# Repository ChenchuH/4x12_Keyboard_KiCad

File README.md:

# 4x12_Keyboard_KiCad
4x12 RP2040 Keyboard

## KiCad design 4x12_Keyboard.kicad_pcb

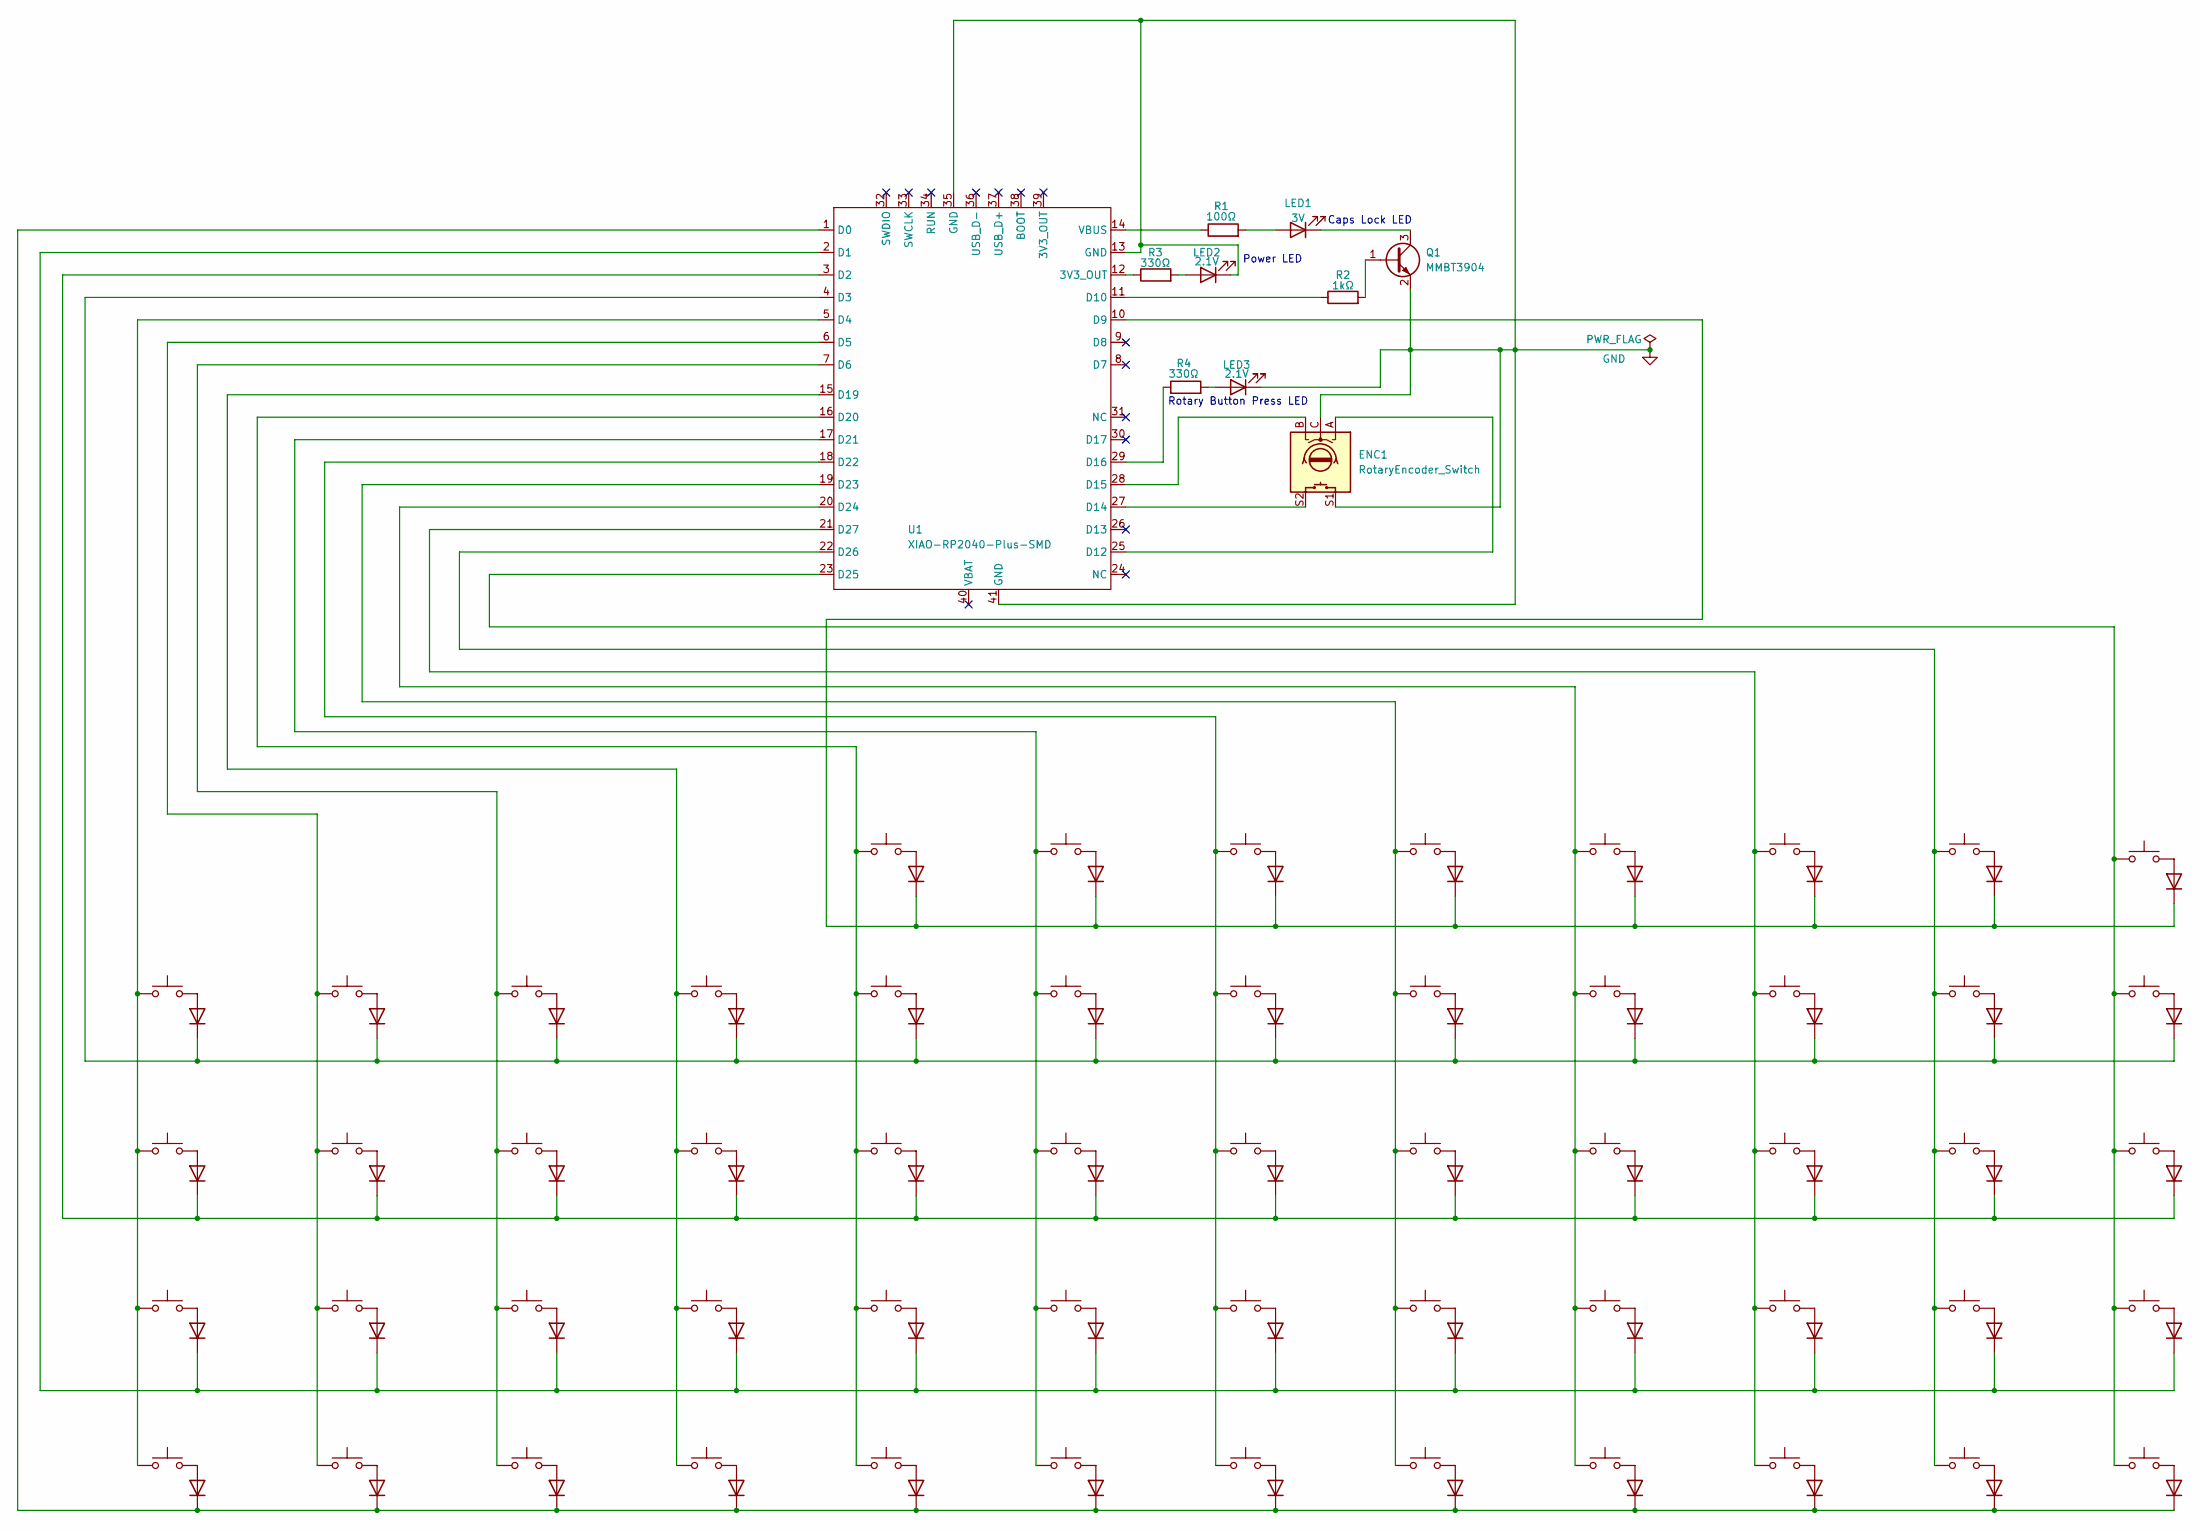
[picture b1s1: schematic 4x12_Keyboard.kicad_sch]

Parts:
D1, D2, D3, D4, D5, D6, D7, D8, D9, D10, D11, D12, D13, D14, D15, D16, D17, D18, D19, D20, D21, D22, D23, D24, D25, D26, D27, D28, D29, D30, D31, D32, D33, D34, D35, D36, D37, D38, D39, D40, D41, D42, D43, D44, D45, D46, D47, D48, D49, D50, D51, D52, D53, D54, D55, D56: D; D_SOD-123
ENC1: RotaryEncoder_Switch; RotaryEncoder_Alps_EC11E-Switch_Vertical_H20mm
LED1: 3V; LED_0805_2012Metric_Pad1.15x1.40mm_HandSolder
LED2, LED3: 2.1V; LED_0805_2012Metric_Pad1.15x1.40mm_HandSolder
Q1: MMBT3904; SOT-23
R1: 100Ω; R_0805_2012Metric_Pad1.20x1.40mm_HandSolder
R2: 1kΩ; R_0805_2012Metric_Pad1.20x1.40mm_HandSolder
R3, R4: 330Ω; R_0805_2012Metric_Pad1.20x1.40mm_HandSolder
SW1, SW2, SW3, SW4, SW5, SW6, SW7, SW8, SW9, SW10, SW11, SW12, SW13, SW14, SW15, SW16, SW17, SW18, SW19, SW20, SW21, SW22, SW23, SW24, SW25, SW26, SW27, SW28, SW29, SW30, SW31, SW32, SW33, SW34, SW35, SW36, SW37, SW38, SW39, SW40, SW41, SW42, SW43, SW44, SW45, SW46, SW47, SW48, SW49, SW50, SW51, SW52, SW53, SW54, SW55, SW56: SW_Push; SW_Cherry_MX_1.00u_PCB
U1: XIAO-RP2040-Plus-SMD

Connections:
GND: ENC1.C, ENC1.S1, LED2.1 (K), LED3.1 (K), Q1.2 (E), U1.13 (GND), U1.35 (GND), U1.41 (GND)
unnamed: D1.2 (A), SW1.2
unnamed: D1.1 (K), D5.1 (K), D9.1 (K), D13.1 (K), D17.1 (K), D21.1 (K), D25.1 (K), D29.1 (K), D33.1 (K), D37.1 (K), D41.1 (K), D45.1 (K), U1.4 (D3)
unnamed: D2.2 (A), SW2.2
unnamed: D3.2 (A), SW3.2
unnamed: D4.2 (A), SW4.2
unnamed: D5.2 (A), SW5.2
unnamed: D6.2 (A), SW6.2
unnamed: D7.2 (A), SW7.2
unnamed: D8.2 (A), SW8.2
unnamed: D9.2 (A), SW9.2
unnamed: D10.2 (A), SW10.2
unnamed: D2.1 (K), D6.1 (K), D10.1 (K), D14.1 (K), D18.1 (K), D22.1 (K), D26.1 (K), D30.1 (K), D34.1 (K), D38.1 (K), D42.1 (K), D46.1 (K), U1.3 (D2)
unnamed: D11.2 (A), SW11.2
unnamed: D3.1 (K), D7.1 (K), D11.1 (K), D15.1 (K), D19.1 (K), D23.1 (K), D27.1 (K), D31.1 (K), D35.1 (K), D39.1 (K), D43.1 (K), D47.1 (K), U1.2 (D1)
unnamed: D12.2 (A), SW12.2
unnamed: D4.1 (K), D8.1 (K), D12.1 (K), D16.1 (K), D20.1 (K), D24.1 (K), D28.1 (K), D32.1 (K), D36.1 (K), D40.1 (K), D44.1 (K), D48.1 (K), U1.1 (D0)
unnamed: D13.2 (A), SW13.2
unnamed: D14.2 (A), SW14.2
unnamed: D15.2 (A), SW15.2
unnamed: D16.2 (A), SW16.2
unnamed: D17.2 (A), SW17.2
unnamed: D18.2 (A), SW18.2
unnamed: D19.2 (A), SW19.2
unnamed: D20.2 (A), SW20.2
unnamed: D21.2 (A), SW21.2
unnamed: D22.2 (A), SW22.2
unnamed: D23.2 (A), SW23.2
unnamed: D24.2 (A), SW24.2
unnamed: D25.2 (A), SW25.2
unnamed: D26.2 (A), SW26.2
unnamed: D27.2 (A), SW27.2
unnamed: D28.2 (A), SW28.2
unnamed: D29.2 (A), SW29.2
unnamed: D30.2 (A), SW30.2
unnamed: D31.2 (A), SW31.2
unnamed: D32.2 (A), SW32.2
unnamed: D33.2 (A), SW33.2
unnamed: D34.2 (A), SW34.2
unnamed: D35.2 (A), SW35.2
unnamed: D36.2 (A), SW36.2
unnamed: D37.2 (A), SW37.2
unnamed: D38.2 (A), SW38.2
unnamed: D39.2 (A), SW39.2
unnamed: D40.2 (A), SW40.2
unnamed: D41.2 (A), SW41.2
unnamed: D42.2 (A), SW42.2
unnamed: D43.2 (A), SW43.2
unnamed: D44.2 (A), SW44.2
unnamed: D45.2 (A), SW45.2
unnamed: D46.2 (A), SW46.2
unnamed: D47.2 (A), SW47.2
unnamed: D48.2 (A), SW48.2
unnamed: D49.2 (A), SW49.2
unnamed: D49.1 (K), D50.1 (K), D51.1 (K), D52.1 (K), D53.1 (K), D54.1 (K), D55.1 (K), D56.1 (K), U1.10 (D9)
unnamed: D50.2 (A), SW50.2
unnamed: D51.2 (A), SW51.2
unnamed: D52.2 (A), SW52.2
unnamed: D53.2 (A), SW53.2
unnamed: D54.2 (A), SW54.2
unnamed: D55.2 (A), SW55.2
unnamed: D56.2 (A), SW56.2
unnamed: LED1.2 (A), R1.2
unnamed: LED1.1 (K), Q1.3 (C)
unnamed: LED2.2 (A), R3.2
unnamed: LED3.2 (A), R4.2
unnamed: Q1.1 (B), R2.2
unnamed: R3.1, U1.12 (3V3_OUT)
unnamed: SW1.1, SW2.1, SW3.1, SW4.1, U1.5 (D4)
unnamed: SW5.1, SW6.1, SW7.1, SW8.1, U1.6 (D5)
unnamed: SW9.1, SW10.1, SW11.1, SW12.1, U1.7 (D6)
unnamed: R2.1, U1.11 (D10)
unnamed: ENC1.A, U1.25 (D12)
unnamed: ENC1.S2, U1.27 (D14)
unnamed: ENC1.B, U1.28 (D15)
unnamed: R4.1, U1.29 (D16)
unnamed: SW13.1, SW14.1, SW15.1, SW16.1, U1.15 (D19)
unnamed: SW17.1, SW18.1, SW19.1, SW20.1, SW49.1, U1.16 (D20)
unnamed: SW21.1, SW22.1, SW23.1, SW24.1, SW50.1, U1.17 (D21)
unnamed: SW25.1, SW26.1, SW27.1, SW28.1, SW51.1, U1.18 (D22)
unnamed: SW29.1, SW30.1, SW31.1, SW32.1, SW52.1, U1.19 (D23)
unnamed: SW33.1, SW34.1, SW35.1, SW36.1, SW53.1, U1.20 (D24)
unnamed: SW45.1, SW46.1, SW47.1, SW48.1, SW56.1, U1.23 (D25)
unnamed: SW41.1, SW42.1, SW43.1, SW44.1, SW55.1, U1.22 (D26)
unnamed: SW37.1, SW38.1, SW39.1, SW40.1, SW54.1, U1.21 (D27)
unnamed: R1.1, U1.14 (VBUS)

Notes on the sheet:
Power LED
Rotary Button Press LED
Caps Lock LED

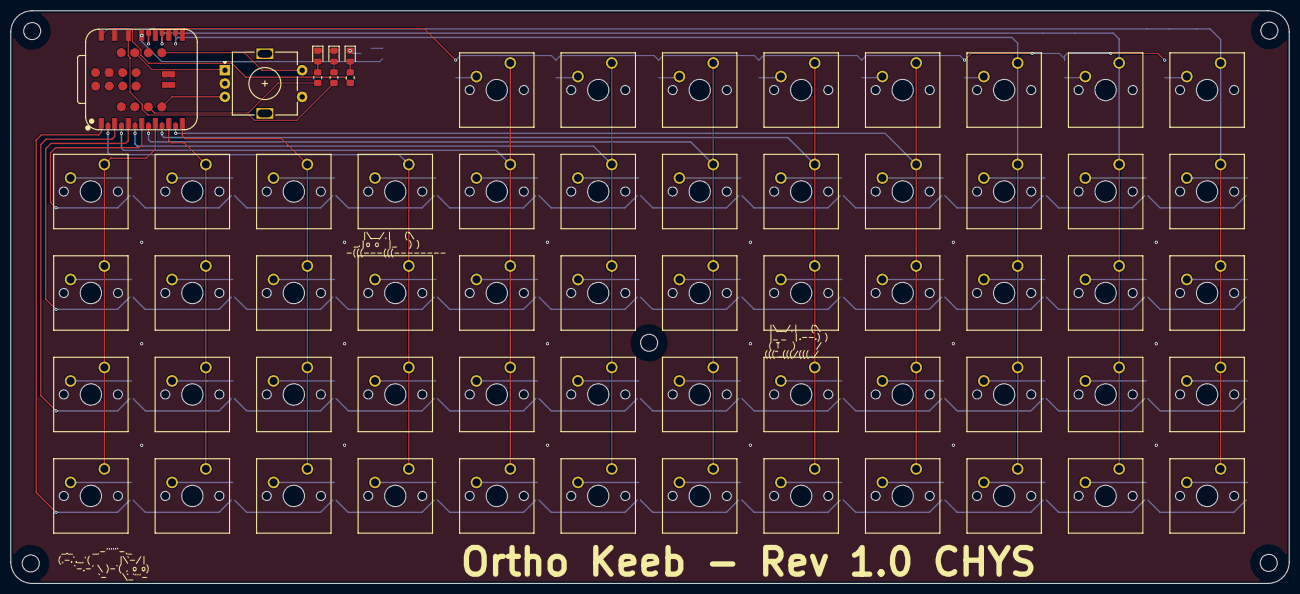
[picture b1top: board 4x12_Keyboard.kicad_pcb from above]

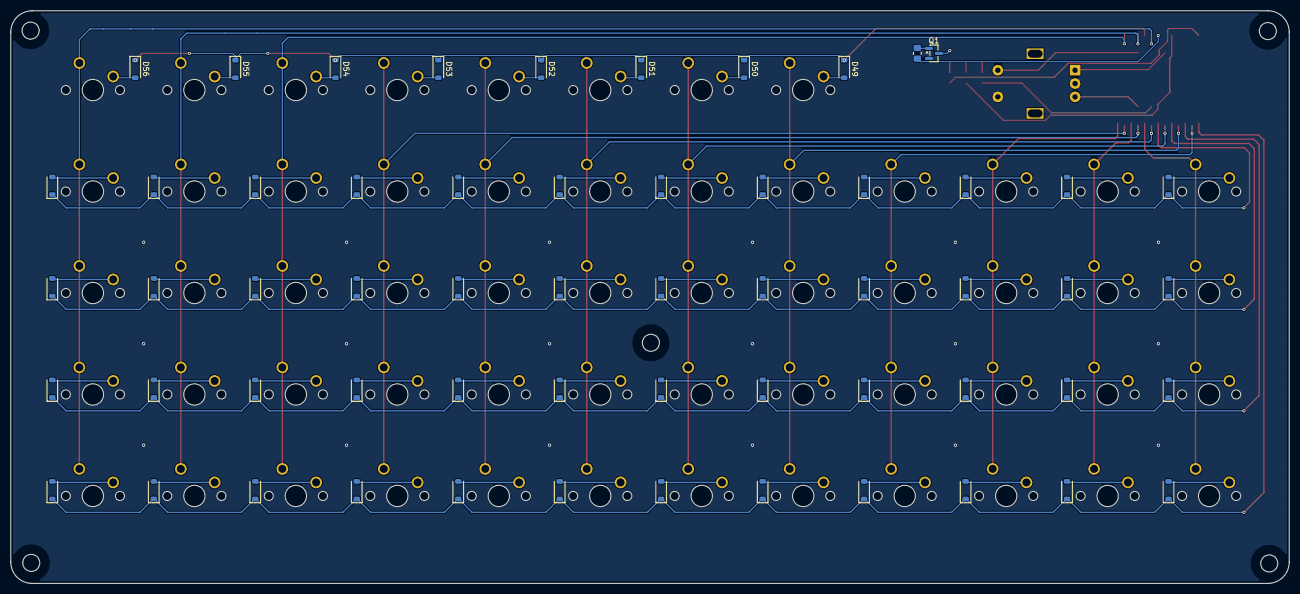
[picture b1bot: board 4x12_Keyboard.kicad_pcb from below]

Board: 2 copper layers, 240.0 x 107.5 mm, 127 parts (58 on the bottom side), 86 nets.

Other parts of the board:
H1, H2, H3, H4, H5: MountingHole_3.2mm_M3
